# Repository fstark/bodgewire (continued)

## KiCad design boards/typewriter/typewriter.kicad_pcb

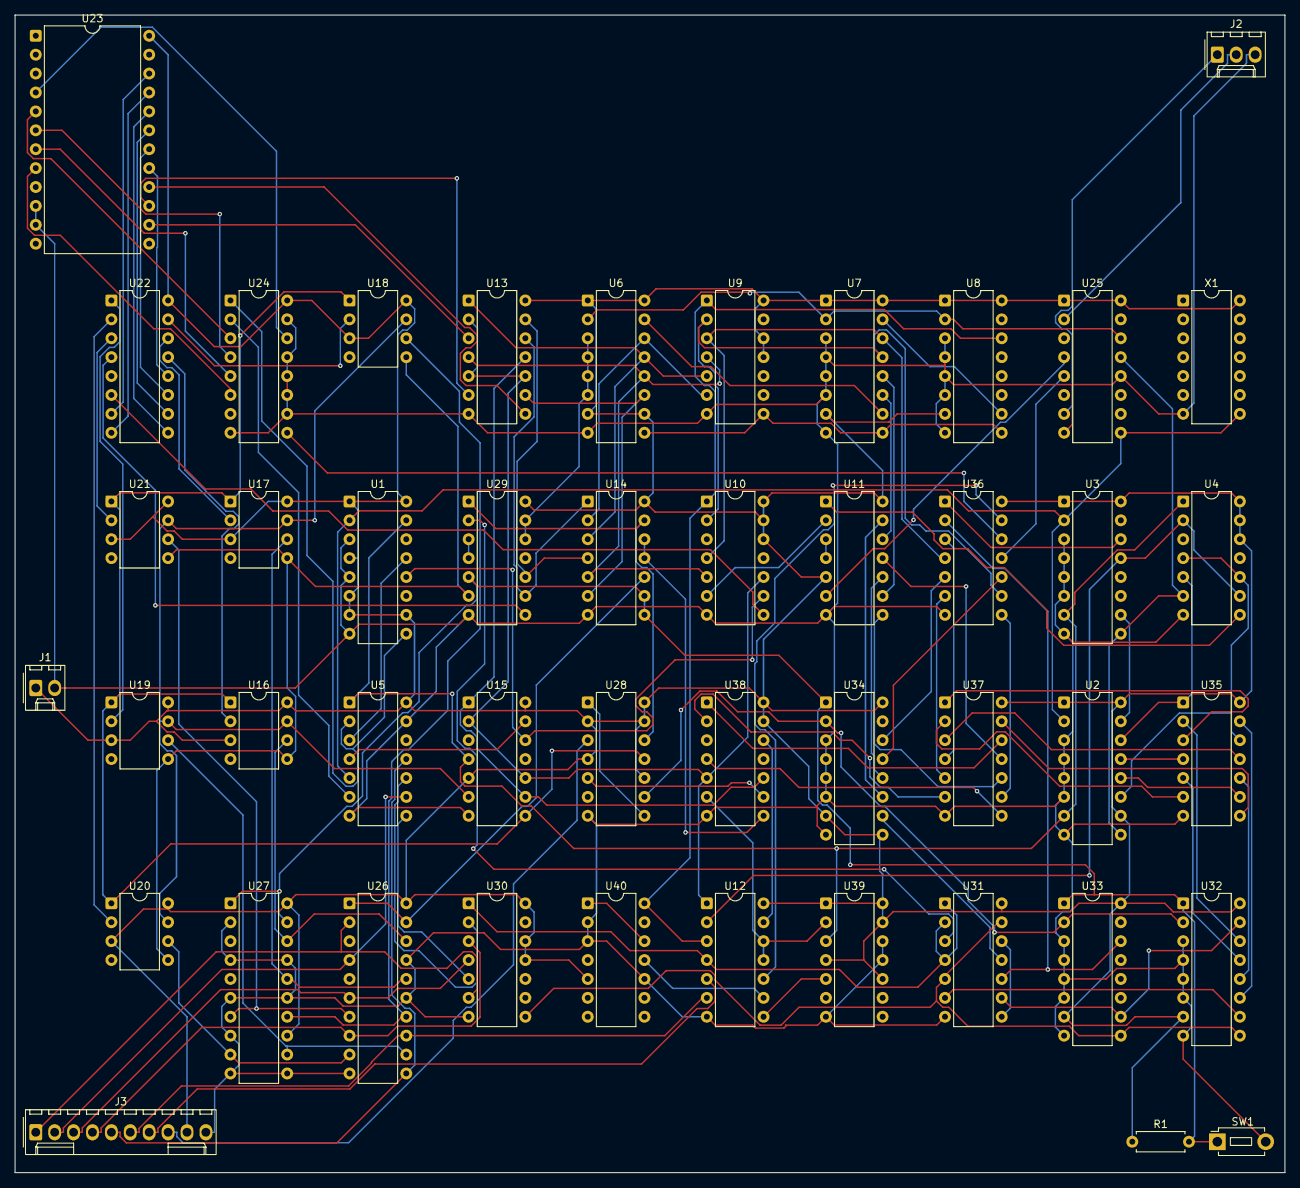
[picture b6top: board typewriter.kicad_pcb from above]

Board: 2 copper layers, 170.6 x 155.5 mm, 46 parts (0 on the bottom side), 125 nets.

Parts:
J1: POWER; Molex_KK-254_AE-6410-02A_1x02_P2.54mm_Vertical
J2: VIDEO; Molex_KK-254_AE-6410-03A_1x03_P2.54mm_Vertical
J3: KEYBOARD; Molex_KK-254_AE-6410-10A_1x10_P2.54mm_Vertical
R1: 4k7; R_Axial_DIN0207_L6.3mm_D2.5mm_P7.62mm_Horizontal
SW1: BUTTON; SW_PUSH_1P1T_6x3.5mm_H5.0_APEM_MJTP1250
U1, U2, U3, U6, U7, U8, U32, U33, U34: 74LS161; DIP-16_W7.62mm
U4, U10, U15, U38: 74LS20; DIP-14_W7.62mm
U5: 74LS04; DIP-14_W7.62mm
U9, U30: 74LS30; DIP-14_W7.62mm
U11, U35, U36: 74LS86; DIP-14_W7.62mm
U12, U14: 74LS02; DIP-14_W7.62mm
U13: 74LS08; DIP-14_W7.62mm
U16, U17, U18, U19, U20, U21: 2524; DIP-8_W7.62mm
U22: 2518; DIP-16_W7.62mm
U23: 2513; DIP-24_W15.24mm
U24: 74LS165; DIP-16_W7.62mm
U25: 74LS175; DIP-16_W7.62mm
U26, U27: 74LS244; DIP-20_W7.62mm
U28, U39: 74LS74; DIP-14_W7.62mm
U29, U31: 74LS00; DIP-14_W7.62mm
U37: 74LS27; DIP-14_W7.62mm
U40: 74LS93; DIP-14_W7.62mm
X1: OSC; DIP-14_W7.62mm

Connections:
ACTIVE: U10.10 (2B), U12.1 (1Y), U13.2 (1B), U13.5 (2B), U13.10 (3B), U15.2 (1B), U15.10 (2B), U38.5 (1D)
ADV: U31.6 (2Y), U32.10 (ENT)
B0: U22.12 (OUT1), U23.17 (A4)
B1: U22.11 (OUT2), U23.18 (A5)
B2: U22.10 (OUT3), U23.19 (A6)
B3: U22.9 (OUT4), U23.20 (A7)
B4: U22.8 (OUT5), U23.21 (A8)
B5: U22.7 (OUT6), U23.22 (A9)
BLINK: U12.9 (3B), U40.11 (QD)
C0: U2.14 (QA), U4.5 (1D), U35.1 (1A)
C1: U2.13 (QB), U35.4 (2A)
C2: U2.12 (QC), U35.9 (3A)
C3: U2.11 (QD), U4.4 (1C), U4.10 (2B), U35.12 (4A)
C4: U3.14 (QA), U36.1 (1A)
C5: U3.13 (QB), U4.2 (1B), U4.9 (2A), U12.2 (1A)
CC: U2.15 (RCO), U3.10 (ENT)
CLEAR: U14.10 (3Y), U26.1 (1OE_N), U26.19 (2OE_N)
CLEAR_N: R1.2, SW1.1, U14.8 (3A), U14.9 (3B), U27.1 (1OE_N), U27.19 (2OE_N), U29.5 (2B), U32.1 (CLR_N), U33.1 (CLR_N), U34.1 (CLR_N)
CLK: U1.2 (CLK), U2.2 (CLK), U3.2 (CLK), U5.5 (3A), U25.9 (CLK), X1.8 (OUT)
CLK_N: U5.6 (3Y), U24.2 (CLK)
CR_N: U30.8 (Y), U31.5 (2B), U31.13 (4B), U32.9 (LOAD_N), U33.9 (LOAD_N)
CTL: U12.4 (2Y), U30.1 (A), U31.1 (1A), U31.2 (1B), U31.4 (2A)
CURSOR_N: U12.8 (3A), U39.5 (1Q)
CUR_SHOW: U12.10 (3Y), U36.13 (4B)
D0: J3.1 (D0), U26.2 (1A1), U30.6 (F)
D1: J3.2 (D1), U5.9 (4A), U26.4 (1A2)
D1_N: U5.8 (4Y), U30.5 (E)
D2: J3.3 (D2), U26.6 (1A3), U30.4 (D)
D3: J3.4 (D3), U26.8 (1A4), U30.3 (C)
D4: J3.5 (D4), U5.11 (5A), U26.11 (2A1)
D4_N: U5.10 (5Y), U30.2 (B)
D5: J3.6 (D5), U12.6 (2B), U26.13 (2A2)
D6: J3.7 (D6), U12.5 (2A)
DOT_END: U1.15 (RCO), U2.7 (ENP), U3.7 (ENP), U4.1 (1A), U5.1 (1A), U15.4 (1C), U39.3 (1CLK)
DOT_LOAD_N: U1.9 (LOAD_N), U5.2 (1Y), U24.1 (SH_LD_N)
EQ0: U37.12 (1Y), U38.1 (1A)
EQ1: U37.6 (2Y), U38.2 (1B)
EQ2: U37.8 (3Y), U38.4 (1C)
F1: U23.4 (O1), U24.14 (D)
F2: U23.5 (O2), U24.3 (E)
F3: U23.6 (O3), U24.4 (F)
F4: U23.7 (O4), U24.5 (G)
F5: U23.8 (O5), U24.6 (H)
FRAME2: U40.1 (CKB), U40.12 (QA)
FRAME_END_N: U6.9 (LOAD_N), U7.9 (LOAD_N), U8.9 (LOAD_N), U9.8 (Y)
GND: J1.2 (GND), J2.3 (GND), J3.10 (GND), SW1.2, U1.3 (A), U1.5 (C), U1.8 (GND), U2.3 (A), U2.4 (B), U2.5 (C), U2.6 (D), U2.8 (GND), U3.3 (A), U3.4 (B), U3.5 (C), U3.6 (D), U3.8 (GND), U4.7 (GND), U5.7 (GND), U5.13 (6A), U6.3 (A), U6.4 (B), U6.5 (C), U6.6 (D), U6.8 (GND), U7.3 (A), U7.4 (B), U7.5 (C), U7.6 (D), U7.8 (GND), U8.3 (A), U8.4 (B), U8.5 (C), U8.6 (D), U8.8 (GND), U9.7 (GND), U10.7 (GND), U11.7 (GND), U12.7 (GND), U13.7 (GND), U14.7 (GND), U15.7 (GND), U23.10 (GND), U23.11 (CE_N), U24.8 (GND), U24.10 (SER), U24.11 (A), U24.12 (B), U24.13 (C), U24.15 (CLK_INH), U25.8 (GND), U25.12 (3D), U26.10 (GND), U26.15 (2A3), U26.17 (2A4), U27.2 (1A1), U27.4 (1A2), U27.6 (1A3), U27.8 (1A4), U27.10 (GND), U27.11 (2A1), U27.15 (2A3), U27.17 (2A4), U28.7 (GND), U29.7 (GND), U29.12 (4A), U29.13 (4B), U30.7 (GND), U31.7 (GND), U32.3 (A), U32.4 (B), U32.5 (C), U32.6 (D), U32.8 (GND), U33.3 (A), U33.4 (B), U33.5 (C), U33.6 (D), U33.8 (GND), U34.3 (A), U34.4 (B), U34.5 (C), U34.6 (D), U34.8 (GND), U35.7 (GND), U36.7 (GND), U37.7 (GND), U38.7 (GND), U39.7 (GND), U39.11 (2CLK), U39.12 (2D), U40.2 (R01), U40.3 (R02), U40.10 (GND), X1.7 (GND)
GO: U14.13 (4Y), U28.12 (2D), U29.1 (1A)
GO_N: U14.11 (4A), U14.12 (4B), U38.8 (2Y)
HSYNC_N: U4.8 (2Y), U11.1 (1A)
KEY: U28.5 (1Q), U38.9 (2A)
LINE_END: U6.2 (CLK), U7.2 (CLK), U8.2 (CLK), U25.14 (4Q_N)
LINE_END_N: U2.9 (LOAD_N), U3.9 (LOAD_N), U4.6 (1Y), U25.13 (4D)
MATCH: U12.13 (4Y), U38.12 (2C)
MATCH_N: U12.11 (4A), U12.12 (4B), U38.6 (1Y), U39.2 (1D)
NE0: U35.3 (1Y), U37.1 (1A)
NE1: U35.6 (2Y), U37.2 (1B)
NE2: U35.8 (3Y), U37.13 (1C)
NE3: U35.11 (4Y), U37.3 (2A)
NE4: U36.3 (1Y), U37.4 (2B)
NE5: U36.6 (2Y), U37.5 (2C)
NE6: U36.8 (3Y), U37.9 (3A)
NE7: U11.8 (3Y), U37.10 (3B)
NE8: U11.11 (4Y), U37.11 (3C)
P0: U16.2 (OUT), U22.13 (IN1)
P1: U17.2 (OUT), U22.14 (IN2)
P2: U18.2 (OUT), U22.15 (IN3)
P3: U19.2 (OUT), U22.1 (IN4)
P4: U20.2 (OUT), U22.2 (IN5)
P5: U21.2 (OUT), U22.3 (IN6)
PHI1_N: U15.6 (1Y), U16.7 (PHI1), U17.7 (PHI1), U18.7 (PHI1), U19.7 (PHI1), U20.7 (PHI1), U21.7 (PHI1)
PHI2_N: U15.8 (2Y), U16.1 (PHI2), U17.1 (PHI2), U18.1 (PHI2), U19.1 (PHI2), U20.1 (PHI2), U21.1 (PHI2), U28.11 (2CLK)
PRINT: U29.2 (1B), U31.3 (1Y)
QB: U1.13 (QB), U5.3 (2A)
QB_N: U5.4 (2Y), U15.13 (2D)
QC: U1.12 (QC), U10.9 (2A), U15.12 (2C)
R1: U13.3 (1Y), U23.14 (A1)
R2: U13.6 (2Y), U23.15 (A2)
R3: U13.8 (3Y), U23.16 (A3)
ROW_CLK: U10.8 (2Y), U22.6 (CLK)
ROW_LOAD_N: U22.4 (REC), U29.8 (3Y)
ROW_TOP: U13.11 (4Y), U15.1 (1A), U15.9 (2A), U38.10 (2B)
STROBE: J3.8 (STROBE), U28.3 (1CLK)
SYNC: U11.3 (1Y), U11.4 (2A)
SYNC_N: J2.2 (SYNC_N), U25.2 (1Q)
SYNC_N_D: U11.6 (2Y), U25.4 (1D)
V0: U6.14 (QA), U9.6 (F), U14.2 (1A)
V1: U6.13 (QB), U9.5 (E), U13.1 (1A), U14.3 (1B)
V01_ZERO: U13.12 (4A), U14.1 (1Y), U29.9 (3A)
V2: U6.12 (QC), U9.4 (D), U10.5 (1D), U13.4 (2A), U14.5 (2A)
V3: U6.11 (QD), U13.9 (3A), U14.6 (2B)
V4: U7.14 (QA), U9.3 (C), U10.4 (1C), U36.4 (2A)
V5: U7.13 (QB), U9.2 (B), U10.2 (1B), U36.9 (3A)
V6: U7.12 (QC), U11.9 (3A)
V7: U7.11 (QD), U11.12 (4A)
V8: U8.14 (QA), U9.1 (A), U10.1 (1A), U12.3 (1B), U40.14 (CKA)
V23_ZERO: U13.13 (4B), U14.4 (2Y), U29.10 (3B)
VC1: U6.15 (RCO), U7.10 (ENT)
VC2: U7.15 (RCO), U8.10 (ENT)
VCC: J1.1 (VCC), J3.9 (VCC), R1.1, U1.1 (CLR_N), U1.4 (B), U1.6 (D), U1.7 (ENP), U1.10 (ENT), U1.16 (VCC), U2.1 (CLR_N), U2.10 (ENT), U2.16 (VCC), U3.1 (CLR_N), U3.16 (VCC), U4.12 (2C), U4.13 (2D), U4.14 (VCC), U5.14 (VCC), U6.1 (CLR_N), U6.7 (ENP), U6.10 (ENT), U6.16 (VCC), U7.1 (CLR_N), U7.7 (ENP), U7.16 (VCC), U8.1 (CLR_N), U8.7 (ENP), U8.16 (VCC), U9.11 (G), U9.12 (H), U9.14 (VCC), U10.12 (2C), U10.13 (2D), U10.14 (VCC), U11.5 (2B), U11.14 (VCC), U12.14 (VCC), U13.14 (VCC), U14.14 (VCC), U15.5 (1D), U15.14 (VCC), U16.3 (READ), U16.8 (VCC), U17.3 (READ), U17.8 (VCC), U18.3 (READ), U18.8 (VCC), U19.3 (READ), U19.8 (VCC), U20.3 (READ), U20.8 (VCC), U21.3 (READ), U21.8 (VCC), U22.16 (VCC), U23.24 (VCC), U24.16 (VCC), U25.1 (CLR_N), U25.16 (VCC), U26.20 (VCC), U27.13 (2A2), U27.20 (VCC), U28.2 (1D), U28.4 (1PRE_N), U28.10 (2PRE_N), U28.13 (2CLR_N), U28.14 (VCC), U29.14 (VCC), U30.11 (G), U30.12 (H), U30.14 (VCC), U31.14 (VCC), U32.7 (ENP), U32.16 (VCC), U33.7 (ENP), U33.16 (VCC), U34.7 (ENP), U34.9 (LOAD_N), U34.16 (VCC), U35.14 (VCC), U36.14 (VCC), U37.14 (VCC), U38.13 (2D), U38.14 (VCC), U39.1 (1CLR_N), U39.4 (1PRE_N), U39.10 (2PRE_N), U39.13 (2CLR_N), U39.14 (VCC), U40.5 (VCC), X1.14 (VCC)
VIDEO: J2.1 (VIDEO), U25.7 (2Q)
VIDEO_D: U24.9 (QH), U36.12 (4A)
VIDEO_M: U25.5 (2D), U36.11 (4Y)
VSYNC_N: U10.6 (1Y), U11.2 (1B)
W0: U16.6 (IN), U26.18 (1Y1), U27.18 (1Y1)
W1: U17.6 (IN), U26.16 (1Y2), U27.16 (1Y2)
W2: U18.6 (IN), U26.14 (1Y3), U27.14 (1Y3)
W3: U19.6 (IN), U26.12 (1Y4), U27.12 (1Y4)
W4: U20.6 (IN), U26.9 (2Y1), U27.9 (2Y1)
W5: U21.6 (IN), U26.7 (2Y2), U27.7 (2Y2)
WR: U28.9 (2Q), U32.2 (CLK), U33.2 (CLK), U34.2 (CLK)
WRITE: U16.5 (WRITE), U17.5 (WRITE), U18.5 (WRITE), U19.5 (WRITE), U20.5 (WRITE), U21.5 (WRITE), U29.6 (2Y)
WRK_N: U29.3 (1Y), U29.4 (2A)
WR_N: U28.1 (1CLR_N), U28.8 (2Q_N)
X0: U32.14 (QA), U35.2 (1B)
X1: U32.13 (QB), U35.5 (2B)
X2: U32.12 (QC), U35.10 (3B)
X3: U32.11 (QD), U35.13 (4B)
X4: U31.10 (3B), U33.14 (QA), U36.2 (1B)
XC_N: U31.8 (3Y), U31.12 (4A)
XRCO: U31.9 (3A), U32.15 (RCO), U33.10 (ENT)
Y0: U34.14 (QA), U36.5 (2B)
Y1: U34.13 (QB), U36.10 (3B)
Y2: U11.10 (3B), U34.12 (QC)
Y3: U11.13 (4B), U34.11 (QD)
YEN: U31.11 (4Y), U34.10 (ENT)

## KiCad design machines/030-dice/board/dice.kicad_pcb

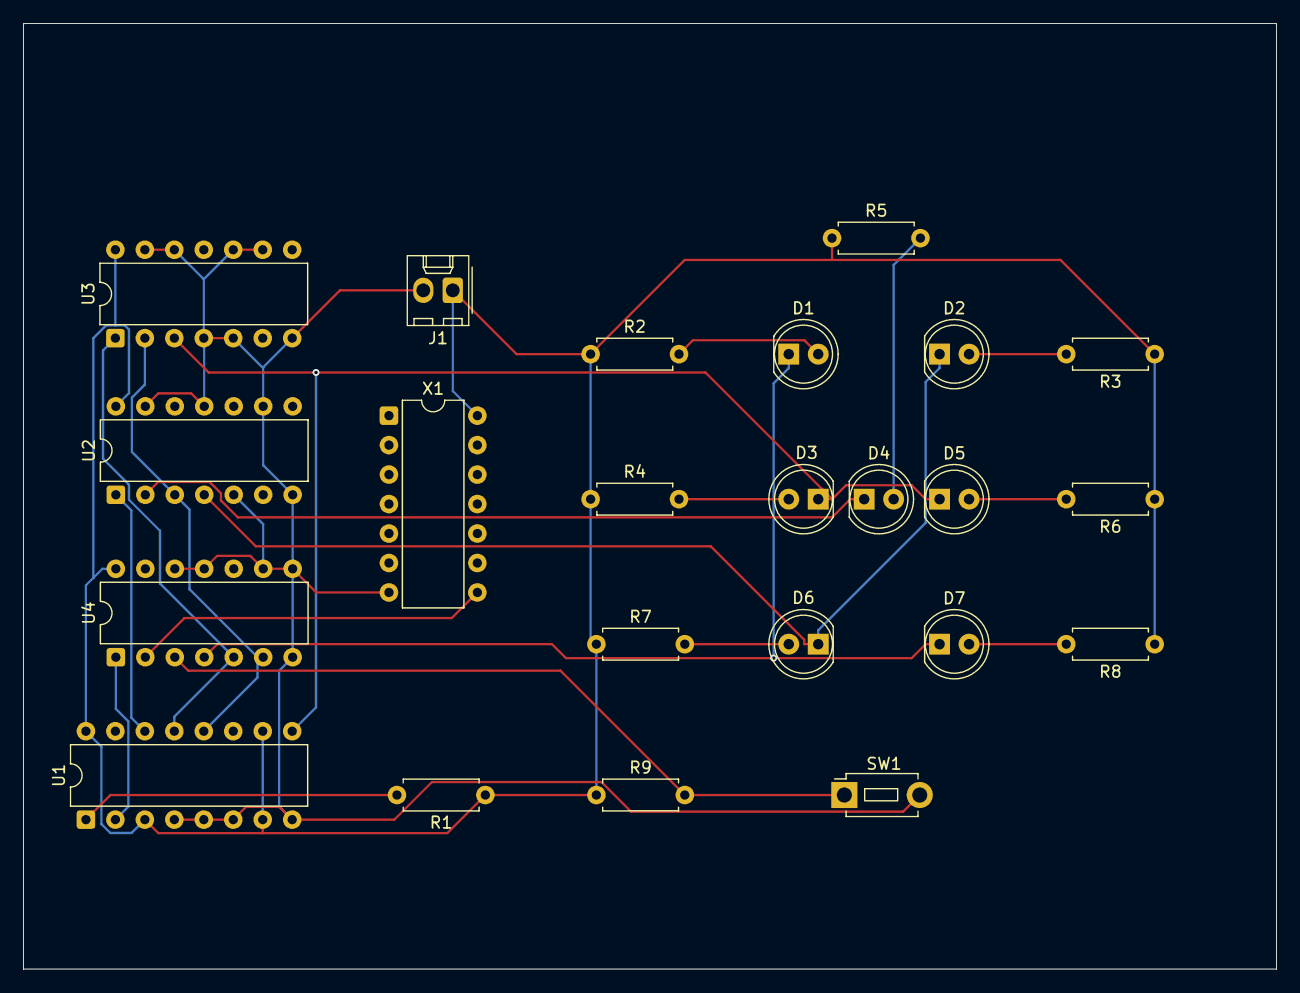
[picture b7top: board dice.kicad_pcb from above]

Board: 2 copper layers, 108.0 x 81.5 mm, 23 parts (0 on the bottom side), 20 nets.

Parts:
D1, D2, D3, D4, D5, D6, D7: LED; LED_D5.0mm
J1: POWER; Molex_KK-254_AE-6410-02A_1x02_P2.54mm_Vertical
R1, R9: 4k7; R_Axial_DIN0207_L6.3mm_D2.5mm_P7.62mm_Horizontal
R2, R3, R4, R5, R6, R7, R8: 330; R_Axial_DIN0207_L6.3mm_D2.5mm_P7.62mm_Horizontal
SW1: BUTTON; SW_PUSH_1P1T_6x3.5mm_H5.0_APEM_MJTP1250
U1: 74LS161; DIP-16_W7.62mm
U2: 74LS04; DIP-14_W7.62mm
U3: 74LS00; DIP-14_W7.62mm
U4: 74LS02; DIP-14_W7.62mm
X1: OSC; DIP-14_W7.62mm

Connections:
BTN_N: R9.2, SW1.1, U4.3 (1B)
CLK: U4.2 (1A), X1.8 (OUT)
FOUR_N: D2.1 (K), D6.1 (K), U2.4 (2Y)
GND: J1.2 (GND), SW1.2, U1.4 (B), U1.5 (C), U1.6 (D), U1.8 (GND), U2.5 (3A), U2.7 (GND), U2.9 (4A), U2.11 (5A), U2.13 (6A), U3.4 (2A), U3.5 (2B), U3.7 (GND), U3.9 (3A), U3.10 (3B), U3.12 (4A), U3.13 (4B), U4.7 (GND), U4.8 (3A), U4.9 (3B), U4.11 (4A), U4.12 (4B), X1.7 (GND)
LED_A1: D1.2 (A), R2.2
LED_A2: D2.2 (A), R3.2
LED_A3: D3.2 (A), R4.2
LED_A4: D4.2 (A), R5.2
LED_A5: D5.2 (A), R6.2
LED_A6: D6.2 (A), R7.2
LED_A7: D7.2 (A), R8.2
N0: U1.14 (QA), U2.1 (1A)
N1: U1.13 (QB), U3.1 (1A), U4.5 (2A)
N2: U1.12 (QC), U2.3 (2A), U3.2 (1B), U4.6 (2B)
ODD_N: D4.1 (K), U2.2 (1Y)
RESET_N: R1.2, U1.1 (CLR_N)
ROLL_CLK: U1.2 (CLK), U4.1 (1Y)
SIX_N: D3.1 (K), D5.1 (K), U1.9 (LOAD_N), U3.3 (1Y)
TWO_N: D1.1 (K), D7.1 (K), U4.4 (2Y)
VCC: J1.1 (VCC), R1.1, R2.1, R3.1, R4.1, R5.1, R6.1, R7.1, R8.1, R9.1, U1.3 (A), U1.7 (ENP), U1.10 (ENT), U1.16 (VCC), U2.14 (VCC), U3.14 (VCC), U4.14 (VCC), X1.14 (VCC)

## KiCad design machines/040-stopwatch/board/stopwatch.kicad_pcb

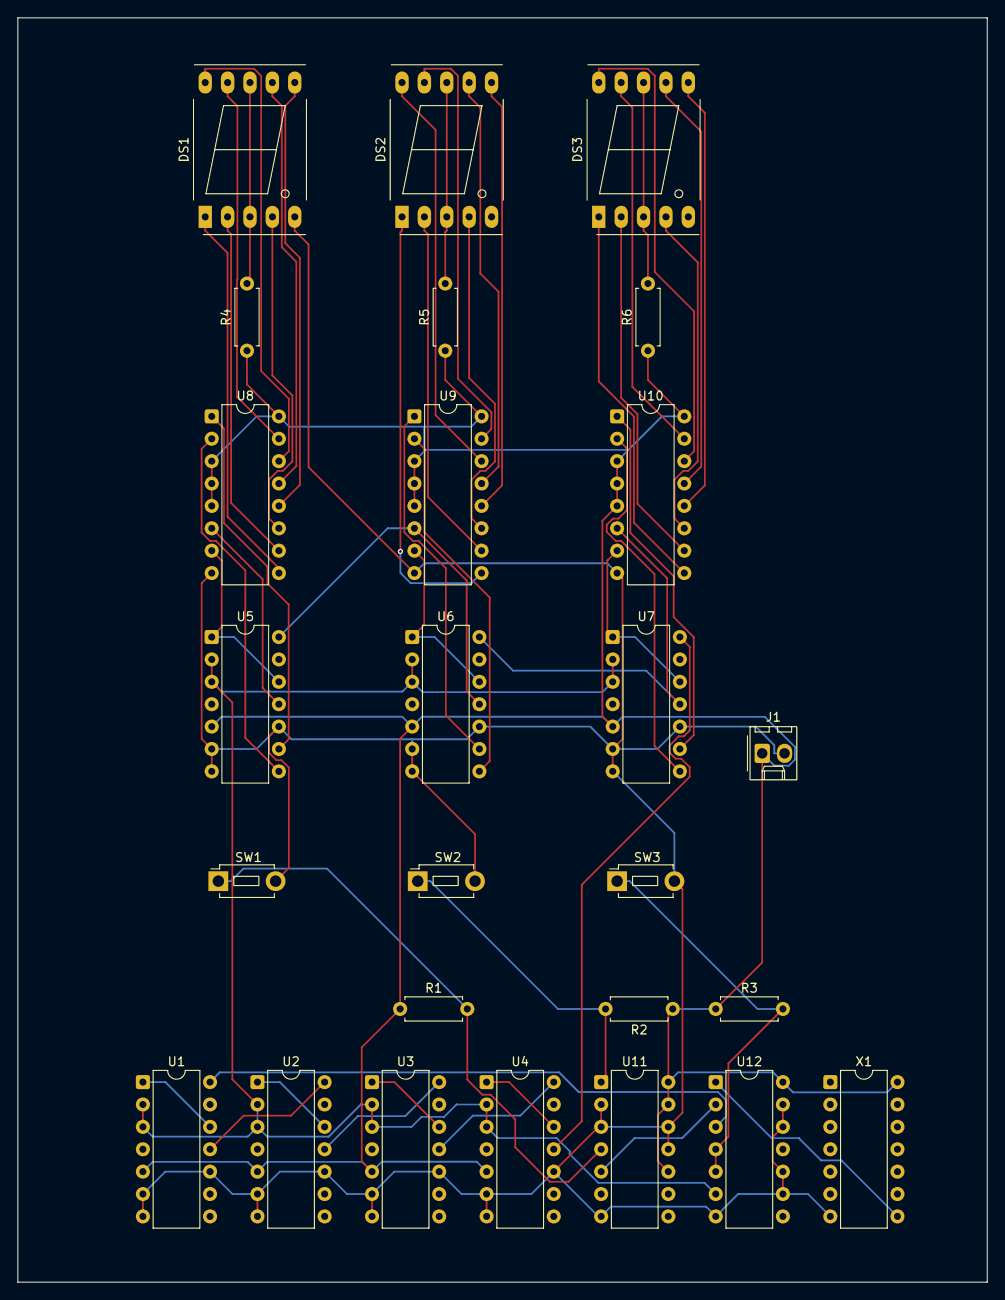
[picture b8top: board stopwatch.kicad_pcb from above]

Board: 2 copper layers, 110.0 x 143.5 mm, 26 parts (0 on the bottom side), 53 nets.

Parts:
DS1, DS2, DS3: DIGIT; 7SegmentLED_LTS6760_LTS6780
J1: POWER; Molex_KK-254_AE-6410-02A_1x02_P2.54mm_Vertical
R1, R2, R3: 4k7; R_Axial_DIN0207_L6.3mm_D2.5mm_P7.62mm_Horizontal
R4, R5, R6: 330; R_Axial_DIN0207_L6.3mm_D2.5mm_P7.62mm_Horizontal
SW1, SW2, SW3: BUTTON; SW_PUSH_1P1T_6x3.5mm_H5.0_APEM_MJTP1250
U1, U2, U3, U4, U5, U6, U7: 74LS90; DIP-14_W7.62mm
U8, U9, U10: 74LS47; DIP-16_W7.62mm
U11: 74LS74; DIP-14_W7.62mm
U12: 74LS00; DIP-14_W7.62mm
X1: OSC; DIP-14_W7.62mm

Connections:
CLK: U12.1 (1A), X1.8 (OUT)
DS1_A: DS1.7 (A), U8.13 (SA_N)
DS1_B: DS1.6 (B), U8.12 (SB_N)
DS1_C: DS1.4 (C), U8.11 (SC_N)
DS1_CA: DS1.3 (CA1), DS1.8 (CA2), R4.2
DS1_D: DS1.2 (D), U8.10 (SD_N)
DS1_E: DS1.1 (E), U8.9 (SE_N)
DS1_F: DS1.9 (F), U8.15 (SF_N)
DS1_G: DS1.10 (G), U8.14 (SG_N)
DS2_A: DS2.7 (A), U9.13 (SA_N)
DS2_B: DS2.6 (B), U9.12 (SB_N)
DS2_C: DS2.4 (C), U9.11 (SC_N)
DS2_CA: DS2.3 (CA1), DS2.8 (CA2), R5.2
DS2_D: DS2.2 (D), U9.10 (SD_N)
DS2_E: DS2.1 (E), U9.9 (SE_N)
DS2_F: DS2.9 (F), U9.15 (SF_N)
DS2_G: DS2.10 (G), U9.14 (SG_N)
DS3_A: DS3.7 (A), U10.13 (SA_N)
DS3_B: DS3.6 (B), U10.12 (SB_N)
DS3_C: DS3.4 (C), U10.11 (SC_N)
DS3_CA: DS3.3 (CA1), DS3.8 (CA2), R6.2
DS3_D: DS3.2 (D), U10.10 (SD_N)
DS3_E: DS3.1 (E), U10.9 (SE_N)
DS3_F: DS3.9 (F), U10.15 (SF_N)
DS3_G: DS3.10 (G), U10.14 (SG_N)
F1K: U3.11 (QD), U4.14 (CKA)
F5K: U3.1 (CKB), U3.12 (QA)
F10K: U2.11 (QD), U3.14 (CKA)
F50K: U2.1 (CKB), U2.12 (QA)
F100: U4.11 (QD), U7.14 (CKA)
F100K: U1.11 (QD), U2.14 (CKA)
F500: U4.1 (CKB), U4.12 (QA)
F500K: U1.1 (CKB), U1.12 (QA)
GCLK: U1.14 (CKA), U12.3 (1Y)
GND: DS1.5 (DP), J1.2 (GND), SW1.2, SW2.2, SW3.2, U1.6 (R91), U1.7 (R92), U1.10 (GND), U2.6 (R91), U2.7 (R92), U2.10 (GND), U3.6 (R91), U3.7 (R92), U3.10 (GND), U4.6 (R91), U4.7 (R92), U4.10 (GND), U5.6 (R91), U5.7 (R92), U5.10 (GND), U6.6 (R91), U6.7 (R92), U6.10 (GND), U7.6 (R91), U7.7 (R92), U7.10 (GND), U8.8 (GND), U9.8 (GND), U10.8 (GND), U11.2 (1D), U11.3 (1CLK), U11.7 (GND), U11.11 (2CLK), U11.12 (2D), U12.7 (GND), U12.9 (3A), U12.10 (3B), U12.12 (4A), U12.13 (4B), X1.7 (GND)
H0: U7.1 (CKB), U7.12 (QA), U10.7 (A)
H1: U7.9 (QB), U10.1 (B)
H2: U7.8 (QC), U10.2 (C)
H3: U6.14 (CKA), U7.11 (QD), U10.6 (D)
RESET: U1.2 (R01), U1.3 (R02), U2.2 (R01), U2.3 (R02), U3.2 (R01), U3.3 (R02), U4.2 (R01), U4.3 (R02), U5.2 (R01), U5.3 (R02), U6.2 (R01), U6.3 (R02), U7.2 (R01), U7.3 (R02), U12.6 (2Y)
RST_N: R3.2, SW3.1, U12.4 (2A), U12.5 (2B)
RUN: U11.5 (1Q), U12.2 (1B)
S0: U5.1 (CKB), U5.12 (QA), U8.7 (A)
S1: U5.9 (QB), U8.1 (B)
S2: U5.8 (QC), U8.2 (C)
S3: U5.11 (QD), U8.6 (D)
START_N: R1.2, SW1.1, U11.4 (1PRE_N)
STOP_N: R2.2, SW2.1, U11.1 (1CLR_N)
T0: U6.1 (CKB), U6.12 (QA), U9.7 (A)
T1: U6.9 (QB), U9.1 (B)
T2: U6.8 (QC), U9.2 (C)
T3: U5.14 (CKA), U6.11 (QD), U9.6 (D)
VCC: J1.1 (VCC), R1.1, R2.1, R3.1, R4.1, R5.1, R6.1, U1.5 (VCC), U2.5 (VCC), U3.5 (VCC), U4.5 (VCC), U5.5 (VCC), U6.5 (VCC), U7.5 (VCC), U8.3 (LT_N), U8.4 (BI_N), U8.5 (RBI_N), U8.16 (VCC), U9.3 (LT_N), U9.4 (BI_N), U9.5 (RBI_N), U9.16 (VCC), U10.3 (LT_N), U10.4 (BI_N), U10.5 (RBI_N), U10.16 (VCC), U11.10 (2PRE_N), U11.13 (2CLR_N), U11.14 (VCC), U12.14 (VCC), X1.14 (VCC)
